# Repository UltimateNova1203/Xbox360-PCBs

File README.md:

# Xbox360-PCBs
PCBs and accessories for the Xbox 360

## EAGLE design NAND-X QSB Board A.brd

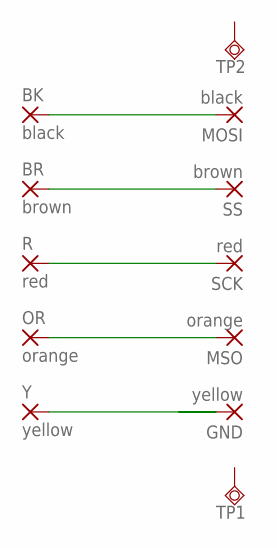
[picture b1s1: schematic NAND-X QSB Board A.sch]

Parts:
BK: black; 1,6/0,8
BR: brown; 1,6/0,8
GND: yellow; SMD1,27-2,54
MOSI: black; SMD1,27-2,54
MSO: orange; SMD1,27-2,54
OR: orange; 1,6/0,8
R: red; 1,6/0,8
SCK: red; SMD1,27-2,54
SS: brown; SMD1,27-2,54
TP1, TP2: TPSQTP11SQ; TP11SQ
Y: yellow; 1,6/0,8

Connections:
unnamed: R.1, SCK.1
unnamed: MSO.1, OR.1
unnamed: BR.1, SS.1
unnamed: GND.1, Y.1
unnamed: BK.1, MOSI.1

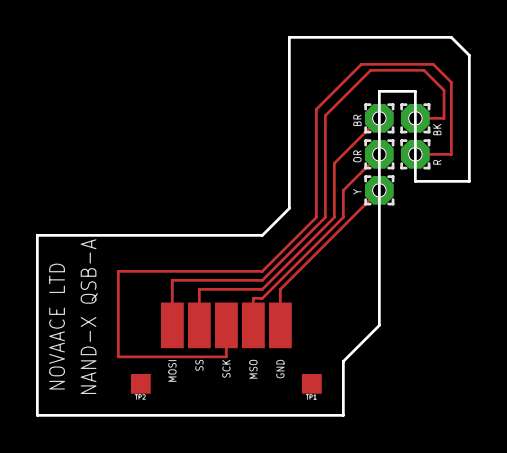
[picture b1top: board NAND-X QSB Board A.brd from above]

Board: 2 copper layers, 24.0 x 21.0 mm, 12 parts (0 on the bottom side), 5 nets.

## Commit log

2020-08-19 Nand-X QSB Board A v1
